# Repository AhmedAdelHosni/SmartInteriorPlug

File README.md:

# SmartInteriorPlug
Smart interior plug is for handling automation of AC lights. This is intended for home automation projects.

The aim of the project is to design a PCB for controlling three AC outputs.

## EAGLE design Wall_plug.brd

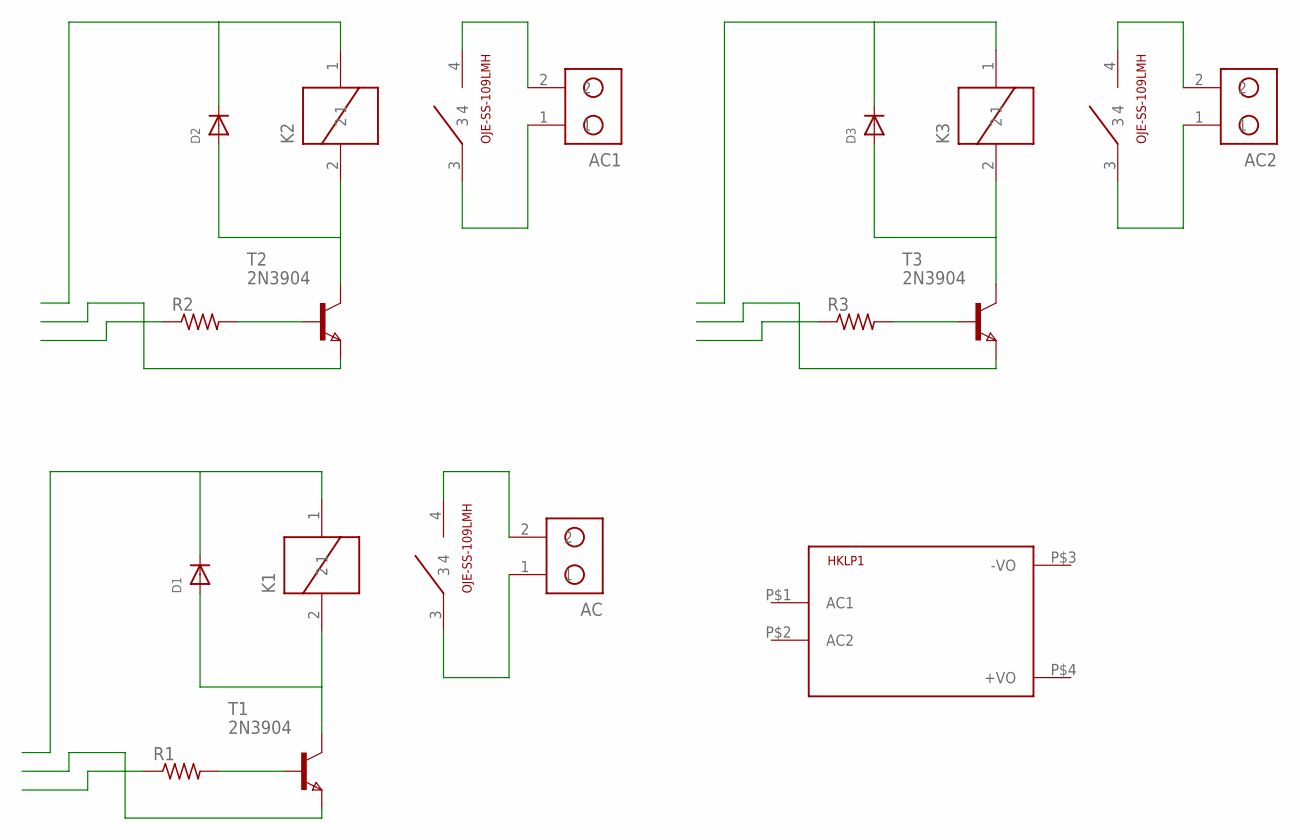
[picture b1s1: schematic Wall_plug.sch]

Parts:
AC, AC1, AC2: TBLOCK1X2
D1, D2, D3: DIODESMA; SMADIODE
HKLP1: HKLPM01
K1, K2, K3: OJE-SS-109LMH
R1, R2, R3: R-US_R0603; R0603
T1, T2, T3: 2N3904; SOT-23

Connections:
unnamed: D1.A, K1.2, T1.1 (C)
unnamed: D1.C, K1.1
unnamed: AC.2, K1.4
unnamed: R2.2, T2.3 (B)
unnamed: R1.2, T1.3 (B)
unnamed: D2.A, K2.2, T2.1 (C)
unnamed: D2.C, K2.1
unnamed: AC.1, K1.3
unnamed: AC1.2, K2.4
unnamed: AC1.1, K2.3
unnamed: R3.2, T3.3 (B)
unnamed: D3.A, K3.2, T3.1 (C)
unnamed: D3.C, K3.1
unnamed: AC2.2, K3.4
unnamed: AC2.1, K3.3

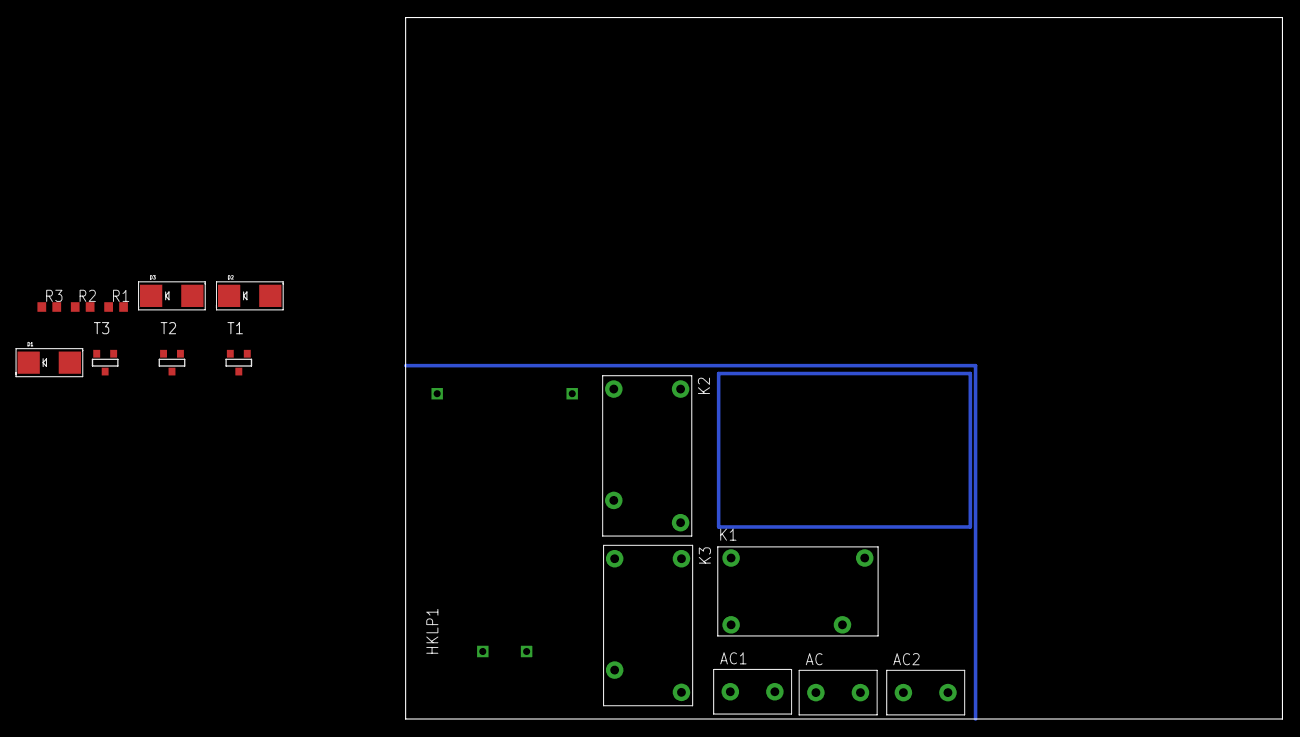
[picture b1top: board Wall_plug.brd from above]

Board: 2 copper layers, 100.0 x 80.0 mm, 16 parts (0 on the bottom side), 15 nets.

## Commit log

2017-11-11 Adding relays, HLK and eByte frame
